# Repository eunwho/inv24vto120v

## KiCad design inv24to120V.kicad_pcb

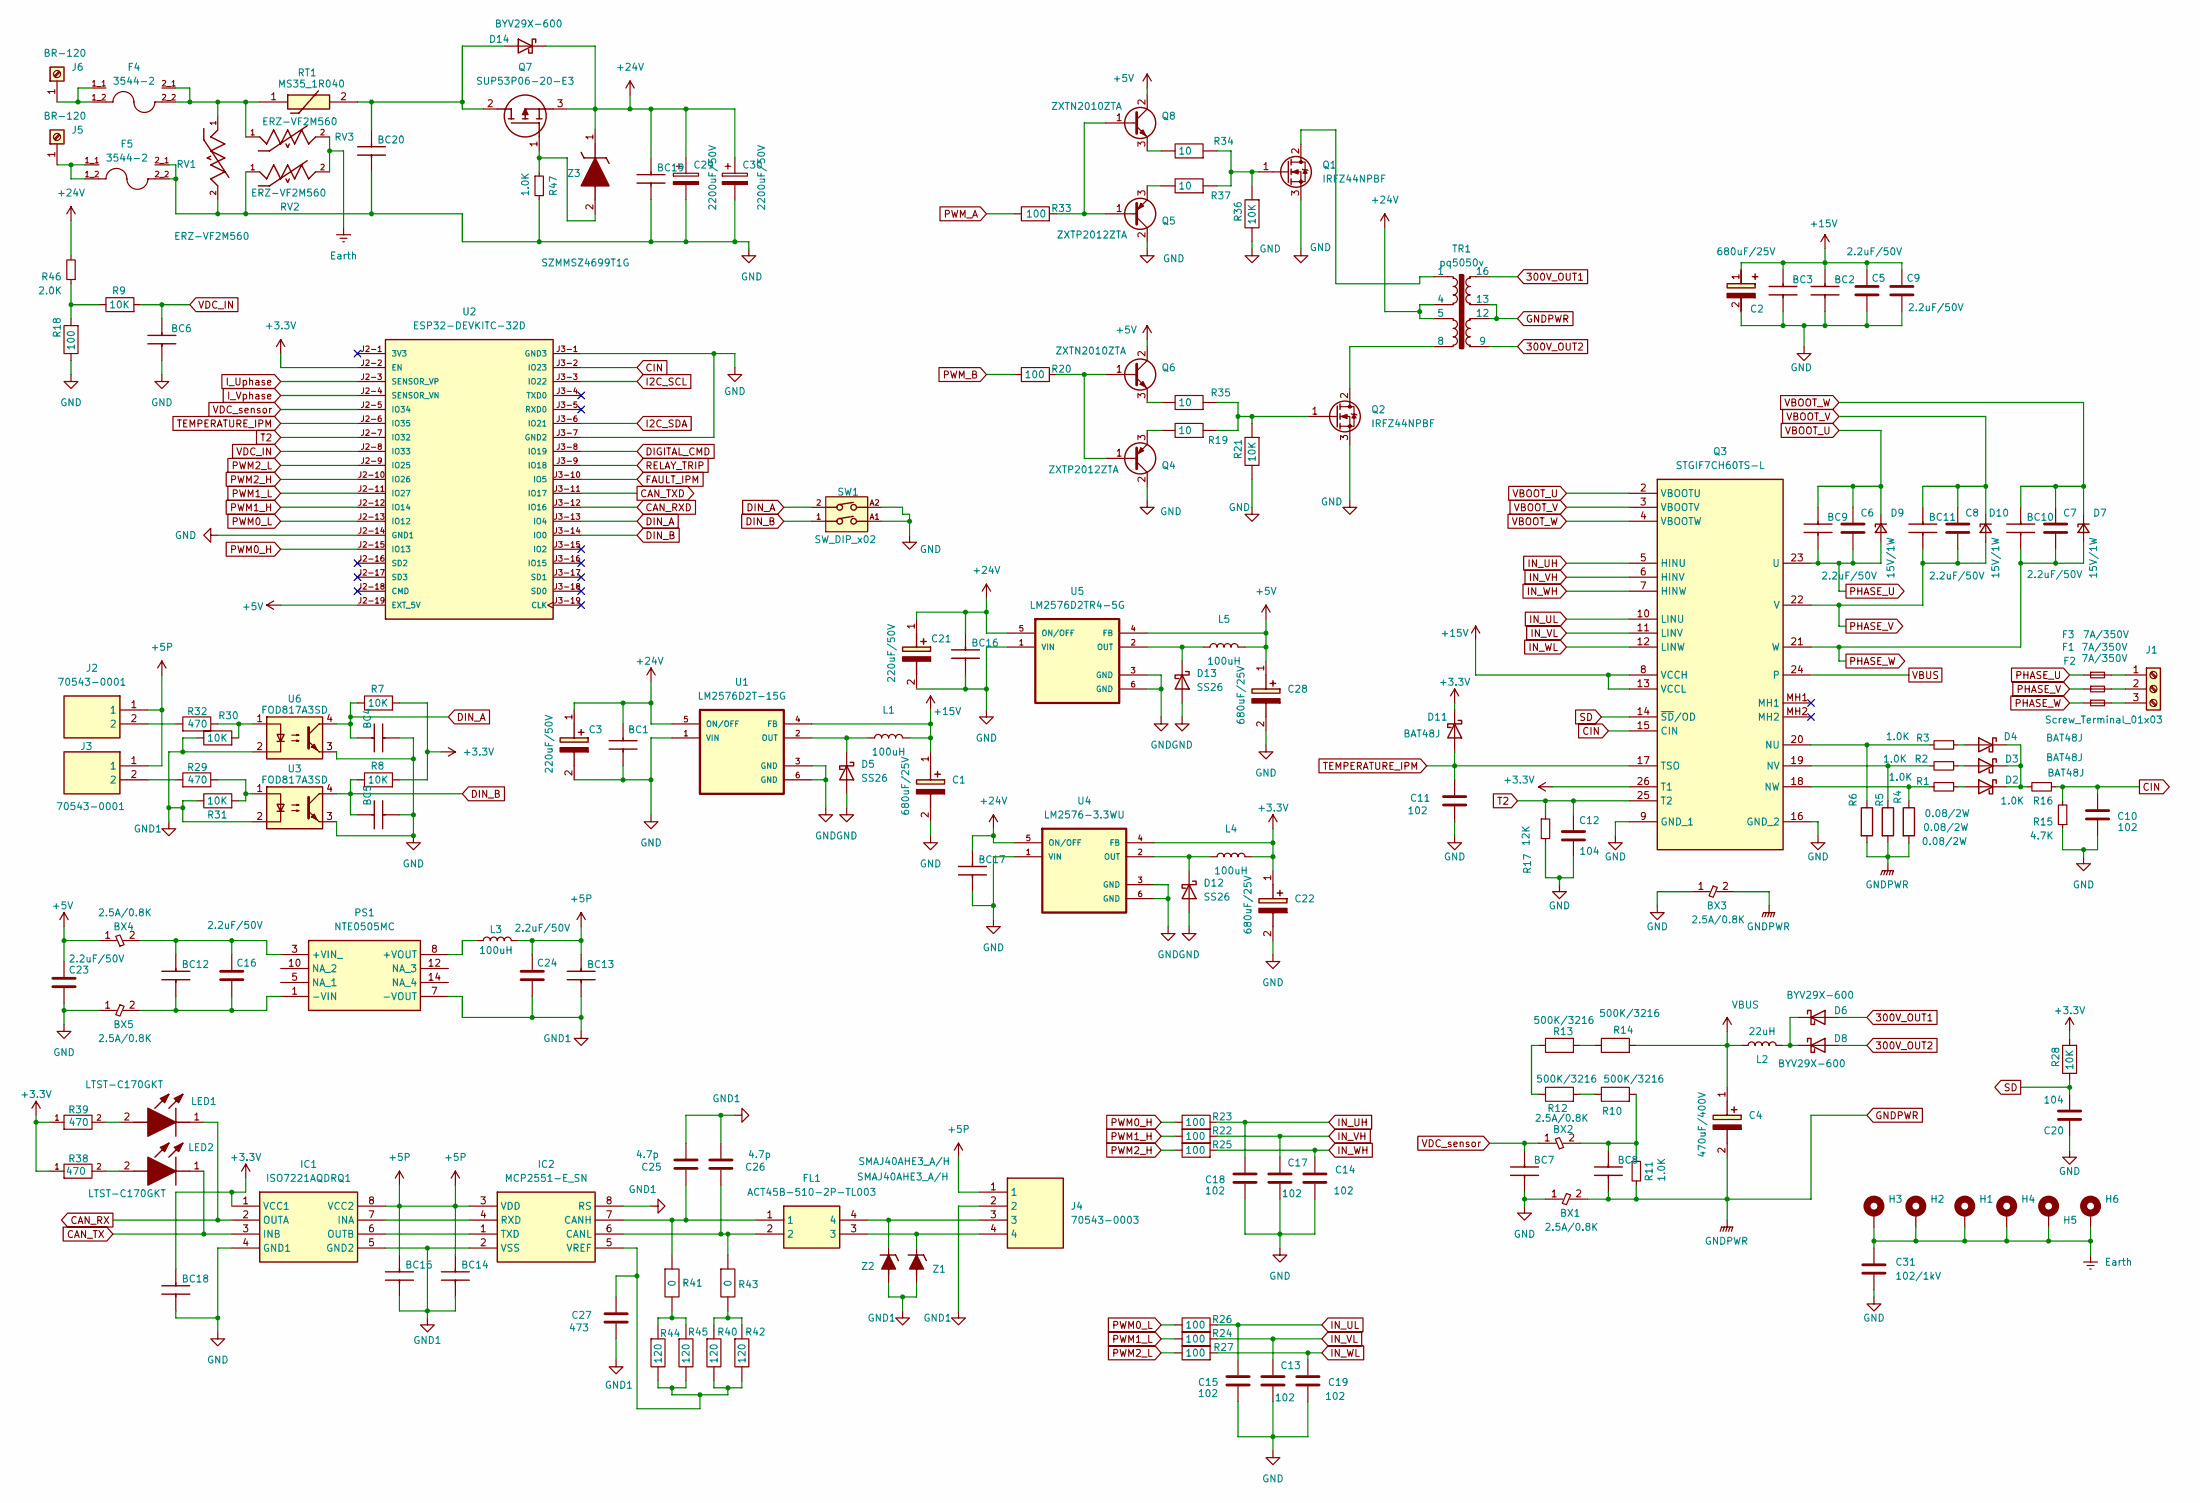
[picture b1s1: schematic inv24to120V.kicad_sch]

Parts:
BC1, BC2, BC3, BC4, BC5, BC6, BC7, BC8, BC9, BC10, BC11, BC12, BC13, BC14, BC15, BC16, BC17, BC18, BC19, BC20: 104/50V; CAPC2012X95N; Manufacturer_Part_Number CL21B104KBCNNNE; Mouser Part Number 187-CL21B104KBCNNNE
BX1, BX2, BX3, BX4, BX5: 2.5A/0.8K; BLM31KN102BH1L; Manufacturer_Part_Number BLM31KN801SH1L; Mouser Part Number 81-BLM31KN801SH1L
C1, C2, C22, C28: 680uF/25V; CP_Elec_16x17.5; Mouser Part Number 594-MAL226099603E3
C3, C21: 220uF/50V; CP_Elec_16x17.5; Mouser Part Number 594-MAL226099603E3
C4: 470uF/400V; CP_Radial_D35.0mm_P10.00mm_SnapIn; Mouser Part Number 647-LGX2G471MELC35
C5, C6, C7, C8, C9, C16, C23, C24: 2.2uF/50V; C_1206_3216Metric_Pad1.33x1.80mm_HandSolder; Manufacturer_Part_Number CL31A225KB9LNNC; Mouser Part Number 187-CL31A225KB9LNNC
C10, C11, C13, C14, C15, C17, C18, C19: 102; C_0805_2012Metric; Manufacturer_Part_Number CL21B102KBCNNNE; Mouser Part Number 187-CL21B104KBCNNNE
C12, C20: 104; C_0805_2012Metric; Manufacturer_Part_Number CL21B104KBCNNNE; Mouser Part Number 187-CL21B104KBCNNNE
C25, C26: 4.7p; C_0805_2012Metric; Manufacturer_Part_Number CL21B047PKBCNNNE; Mouser Part Number 187-CL21B473KBCNNNE
C27: 473; C_0805_2012Metric; Manufacturer_Part_Number CL21B473KBCNNNE; Mouser Part Number 187-CL21B473KBCNNNE
C29, C30: 2200uF/50V; CP_Radial_D18.0mm_P7.50mm; Manufacturer_Part_Number NXA 50V 2200uF
C31: 102/1kV; C_1812_4532Metric_Pad1.57x3.40mm_HandSolder; Manufacturer_Part_Number VJ1808Y103KXGAT; Mouser Part Number 77-VJ1808Y103KXGAT
D2, D3, D4, D11: BAT48J; D_SOD-323_HandSoldering; Mouser Part Number 511-BAT48JFILM
D5, D12, D13: SS26; DIOM5127X229N; Mouser Part Number 78-SS26SHE3_B/H
D6, D8: BYV29X-600; TO-220-2_Horizontal_TabUp; Mouser Part Number 771-BYV29X-600127
D7, D9, D10: 15V/1W; D_SMA_Handsoldering; Manufacturer_Part_Number SZ1SMA5929BT3G; Mouser Part Number 863-SZ1SMA5929BT3G
D14: BYV29X-600; TO507P1020X460X2000-2; Mouser Part Number 771-BYV29X-600127
F1, F2, F3: 7A/350V; Fuse_2512_6332Metric_Pad1.52x3.35mm_HandSolder; Mouser Part Number 530-0679H7000-05
F4, F5: 3544-2; FUSE_3544-2; Mouser Part Number 534-3544-2
FL1: ACT45B-510-2P-TL003; ACT45B1012PTL003; Mouser Part Number 810-ACT45B5102PTL003
H1, H2, H3, H4, H5, H6: MountingHole_Pad; MountingHole_4.3mm_M4_Pad_Via
IC1: ISO7221AQDRQ1; SOIC127P600X175-8N; Mouser Part Number 595-ISO7221AQDRQ1
IC2: MCP2551-E_SN; SOIC127P600X175-8N; Mouser Part Number 579-MCP2551-E/SN
J1: Screw_Terminal_01x03; TerminalBlock_Dinkle_DT-55-B01X-03_P10.00mm; Manufacturer_Part_Number BR-1000C(3핀); Mouser Part Number 디바이스마트 BR-1000C(3핀)
J2, J3: 70543-0001; SHDR2W64P0X254_1X2_737X660X1181P; Mouser Part Number 538-70543-0001
J4: 70543-0003; SHDR4W97P0X254_1X4_1271X660X1143P; Mouser Part Number 538-70543-0003
J5, J6: BR-120; Wuerth_REDCUBE-THR_WP-THRBU_74650073_THR; Manufacturer_Part_Number BR-120
L1, L3, L4, L5: 100uH; INDPM120120X600N; Manufacturer_Part_Number 7447706101; Mouser Part Number 710-7447706101
L2: 22uH; IND_HCTI-10-20.0; Manufacturer_Part_Number RING COIL 21파이(22uH)
LED1, LED2: LTST-C170GKT; LEDC2012X120N; Mouser Part Number 859-LTST-C170GKT
PS1: NTE0505MC; Mouser Part Number 580-NTE0505MC
Q1, Q2: IRFZ44NPBF; TO-220-3_Horizontal_TabUp; Manufacturer_Part_Number IRFZ44NPBF; Mouser Part Number 942-IRFZ44NPBF
Q3: STGIF7CH60TS-L; STGIB20M60TSL; Mouser Part Number 511-STGIF7CH60TS-L
Q4, Q5: ZXTP2012ZTA; SOT-89-3; Manufacturer_Part_Number ZXTP2012ZTA; Mouser Part Number 522-ZXTP2012ZTA
Q6, Q8: ZXTN2010ZTA; SOT-89-3; Manufacturer_Part_Number ZXTN2010ZTA; Mouser Part Number 522-ZXTN2010ZTA
Q7: SUP53P06-20-E3; TO-220-3_Horizontal_TabUp; Manufacturer_Part_Number SUP53P06-20-E3; Mouser Part Number 781-SUP53P06-20-E3
R1, R2, R3, R11, R16, R47: 1.0K; R_1206_3216Metric_Pad1.30x1.75mm_HandSolder; Mouser Part Number 71-RCC12061K00FKEA
R4, R5, R6: 0.08/2W; R_2816_7142Metric_Pad3.20x4.45mm_HandSolder; Mouser Part Number 71-WSL2816R0800FEH
R7, R8, R9, R21, R28, R30, R31, R36: 10K; R_0805_2012Metric_Pad1.20x1.40mm_HandSolder; Manufacturer_Part_Number RC2012J103CS; Mouser Part Number Nop
R10, R12, R13, R14: 500K/3216; R_1206_3216Metric_Pad1.30x1.75mm_HandSolder; Manufacturer_Part_Number CRMA1206AF500KFKEF; Mouser Part Number 71-CRMA1206AF500KFKF
R15: 4.7K; R_1206_3216Metric_Pad1.30x1.75mm_HandSolder; Mouser Part Number 71-RCC12064K70FKEA
R17: 12K; R_1206_3216Metric_Pad1.30x1.75mm_HandSolder; Mouser Part Number 71-RCC120612K0FKEA
R18, R20, R22, R23, R24, R25, R26, R27, R33: 100; R_0805_2012Metric_Pad1.20x1.40mm_HandSolder; Manufacturer_Part_Number RC2012J101CS; Mouser Part Number Nop
R19, R34, R35, R37: 10; R_0805_2012Metric_Pad1.20x1.40mm_HandSolder; Manufacturer_Part_Number RC2012J100CS; Mouser Part Number Nop
R29, R32, R38, R39: 470; R_0805_2012Metric_Pad1.20x1.40mm_HandSolder; Manufacturer_Part_Number RC2012J121CS; Mouser Part Number Nop
R40, R42, R44, R45: 120; R_0805_2012Metric_Pad1.20x1.40mm_HandSolder; Manufacturer_Part_Number RC2012J121CS; Mouser Part Number Nop
R41, R43: 0; R_0805_2012Metric_Pad1.20x1.40mm_HandSolder; Manufacturer_Part_Number RC2012J000CS; Mouser Part Number Nop
R46: 2.0K; R_1206_3216Metric_Pad1.30x1.75mm_HandSolder; Mouser Part Number 71-RCC12062K00FKEA
RT1: MS35_1R040; MS351R040; Manufacturer_Part_Number MS35 1R040; Mouser Part Number 995-MS35-1R040
RV1, RV2, RV3: ERZ-VF2M560; VAR_ERZ-VF2M560; Manufacturer_Part_Number ERZ-VF2M560; Mouser Part Number 667-ERZ-VF2M560
SW1: SW_DIP_x02; 418117270902; Manufacturer_Part_Number 418117270902; Mouser Part Number 710-418117270902
TR1: pq5050v; pq5050h; Manufacturer_Part_Number PQ5050-24-300-6PV; Mouser Part Number Nop
U1: LM2576D2T-15G; KTT0005B; Manufacturer_Part_Number LM2576D2T-15G; Mouser Part Number 863-LM2576D2T-15G
U2: ESP32-DEVKITC-32D; MODULE_ESP32-DEVKITC-32D; Manufacturer_Part_Number DLT-dspModule_241; Mouser Part Number Nop
U3, U6: FOD817A3SD; PDIP4GW_709AH_ONS-M; Manufacturer_Part_Number 호: FOD817A3SD; Mouser Part Number 512-FOD817A3SD
U4: LM2576-3.3WU; KTT0005B; Manufacturer_Part_Number LM2576-3.3WU; Mouser Part Number 998-LM2576-3.3WU
U5: LM2576D2TR4-5G; KTT0005B; Manufacturer_Part_Number LM2576D2TR4-5G; Mouser Part Number 863-LM2576D2TR4-5G
Z1, Z2: SMAJ40AHE3_A/H; DIOM5027X244N; Mouser Part Number 78-SMAJ40AHE3_A/H
Z3: SZMMSZ4699T1G; SOD3716X135N; Manufacturer_Part_Number SZMMSZ4699T1G; Mouser Part Number 863-SZMMSZ4699T1G

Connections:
300V_OUT1: D6.2 (A), TR1.16
300V_OUT2: D8.2 (A), TR1.9
+3.3V: BC18.1, C22.1 (+), D11.1 (K), IC1.1 (VCC1), L4.2, Q3.26 (T1), R7.1, R8.1, R28.1, R38.1, R39.1, U2.J2-2 (EN), U4.4 (FB)
+5P: BC13.1, BC14.1, BC15.1, C24.1, IC1.8 (VCC2), IC2.3 (VDD), J2.1, J3.1, J4.1, L3.2
+5V: BX4.1, C23.1, C28.1 (+), L5.2, Q6.2 (C), Q8.2 (C), U2.J2-19 (EXT_5V), U5.4 (FB)
+15V: BC2.1, BC3.1, C1.1 (+), C2.1 (+), C5.1, C9.1, L1.2, Q3.8 (VCCH), Q3.13 (VCCL), U1.4 (FB)
+24V: BC1.1, BC16.1, BC17.1, BC19.1, C3.1 (+), C21.1 (+), C29.1, C30.1, D14.1 (K), Q7.3 (S), R46.2, TR1.4, TR1.5, U1.5 (ON/OFF), U4.5 (ON/OFF), U5.5 (ON/OFF), Z3.1 (K)
CAN_RX: IC1.2 (OUTA), LED1.1 (K)
CAN_RXD: U2.J3-12 (IO16)
CAN_TX: IC1.3 (INB), LED2.1 (K)
CAN_TXD: U2.J3-11 (IO17)
CIN: C10.1, Q3.15 (CIN), R15.2, R16.1, U2.J3-2 (IO23)
DIGITAL_CMD: U2.J3-8 (IO19)
DIN_A: BC4.1, R7.2, SW1.2, U2.J3-13 (IO4), U6.4
DIN_B: BC5.1, R8.2, SW1.1, U2.J3-14 (IO0), U3.4
Earth: C31.1, H1.1, H2.1, H3.1, H4.1, H5.1, H6.1, RV2.2, RV3.2
FAULT_IPM: U2.J3-10 (IO5)
GND: BC1.2, BC2.2, BC3.2, BC4.2, BC5.2, BC6.2, BC7.2, BC16.2, BC17.2, BC18.2, BC19.2, BC20.2, BX1.1, BX3.1, BX5.1, C1.2 (-), C2.2 (-), C3.2 (-), C5.2, C9.2, C10.2, C11.2, C12.2, C13.2, C14.2, C15.2, C17.2, C18.2, C19.2, C20.1, C21.2 (-), C22.2 (-), C23.2, C28.2 (-), C29.2, C30.2, C31.2, D5.2 (A), D12.2 (A), D13.2 (A), F5.2_1, F5.2_2, IC1.4 (GND1), Q1.3 (S), Q2.3 (S), Q3.9 (GND_1), Q3.16 (GND_2), Q4.2 (C), Q5.2 (C), R15.1, R17.2, R18.2, R21.2, R36.2, R47.2, RV1.2, RV2.1, SW1.A1, SW1.A2, U1.1 (VIN), U1.3 (GND), U1.6 (GND), U2.J2-14 (GND1), U2.J3-1 (GND3), U2.J3-7 (GND2), U3.3, U4.1 (VIN), U4.3 (GND), U4.6 (GND), U5.1 (VIN), U5.3 (GND), U5.6 (GND), U6.3
GND1: BC13.2, BC14.2, BC15.2, C24.2, C25.2, C26.2, C27.2, IC1.5 (GND2), IC2.2 (VSS), IC2.8 (RS), J4.2, PS1.7 (-VOUT), R30.2, R31.2, U3.2, U6.2, Z1.2 (A), Z2.2 (A)
GNDPWR: BC8.2, BX1.2, BX3.2, C4.2 (-), R4.2, R5.2, R6.2, R11.2, TR1.12, TR1.13
I2C_SCL: U2.J3-3 (IO22)
I2C_SDA: U2.J3-6 (IO21)
IN_UH: C18.1, Q3.5 (HINU), R23.1
IN_UL: C15.1, Q3.10 (LINU), R26.1
IN_VH: C17.1, Q3.6 (HINV), R22.1
IN_VL: C13.1, Q3.11 (LINV), R24.1
IN_WH: C14.1, Q3.7 (HINW), R25.1
IN_WL: C19.1, Q3.12 (LINW), R27.1
I_Uphase: U2.J2-3 (SENSOR_VP)
I_Vphase: U2.J2-4 (SENSOR_VN)
unnamed: BC8.1, BX2.2, R10.1, R11.1
unnamed: BC20.1, D14.2 (A), Q7.2 (D), RT1.2
unnamed: D12.1 (K), L4.1, U4.2 (OUT)
unnamed: D13.1 (K), L5.1, U5.2 (OUT)
unnamed: D6.1 (K), D8.1 (K), L2.2
unnamed: D5.1 (K), L1.1, U1.2 (OUT)
unnamed: D2.2 (A), R1.1
unnamed: D2.1 (K), D3.1 (K), D4.1 (K), R16.2
unnamed: D3.2 (A), R2.1
unnamed: D4.2 (A), R3.1
unnamed: F4.2_1, F4.2_2, RT1.1, RV1.1, RV3.1
unnamed: C25.1, FL1.1, IC2.7 (CANH), R41.1
unnamed: C26.1, FL1.2, IC2.6 (CANL), R43.1
unnamed: IC1.7 (INA), IC2.4 (RXD)
unnamed: IC1.6 (OUTB), IC2.1 (TXD)
unnamed: C27.1, IC2.5 (VREF), R40.2, R42.2, R44.2, R45.2
unnamed: J2.2, R32.1
unnamed: J3.2, R29.1
unnamed: F3.2, J1.1
unnamed: F1.2, J1.2
unnamed: F2.2, J1.3
unnamed: F5.1_1, F5.1_2, J5.1
unnamed: F4.1_1, F4.1_2, J6.1
unnamed: LED1.2 (A), R39.2
unnamed: LED2.2 (A), R38.2
unnamed: BC12.1, BX4.2, C16.1, PS1.3 (+VIN_)
unnamed: L3.1, PS1.8 (+VOUT)
unnamed: BC12.2, BX5.2, C16.2, PS1.1 (-VIN)
unnamed: Q1.2 (D), TR1.1
unnamed: Q1.1 (G), R34.1, R36.1, R37.1
unnamed: Q2.2 (D), TR1.8
unnamed: Q2.1 (G), R19.1, R21.1, R35.1
unnamed: Q5.1 (B), Q8.1 (B), R33.1
unnamed: Q8.3 (E), R34.2
unnamed: Q4.1 (B), Q6.1 (B), R20.1
unnamed: Q6.3 (E), R35.2
unnamed: Q5.3 (E), R37.2
unnamed: Q4.3 (E), R19.2
unnamed: Q7.1 (G), R47.1, Z3.2 (A)
unnamed: Q3.20 (NU), R3.2, R6.1
unnamed: Q3.19 (NV), R2.2, R5.1
unnamed: Q3.18 (NW), R1.2, R4.1
unnamed: R41.2, R44.1, R45.1
unnamed: R40.1, R42.1, R43.2
unnamed: R13.1, R14.2
unnamed: R12.2, R13.2
unnamed: R10.2, R12.1
unnamed: R9.2, R18.1, R46.1
unnamed: R30.1, R32.2, U6.1
unnamed: R29.2, R31.1, U3.1
unnamed: FL1.3, J4.4, Z1.1 (K)
unnamed: FL1.4, J4.3, Z2.1 (K)
PHASE_U: BC9.2, C6.2, D9.2 (A), F3.1, Q3.23 (U); also elsewhere on the board
PHASE_V: BC11.2, C8.2, D10.2 (A), F1.1, Q3.22 (V); also elsewhere on the board
PHASE_W: BC10.2, C7.2, D7.2 (A), F2.1, Q3.21 (W)
PWM0_H: R23.2, U2.J2-15 (IO13)
PWM0_L: R26.2, U2.J2-13 (IO12)
PWM1_H: R22.2, U2.J2-12 (IO14)
PWM1_L: R24.2, U2.J2-11 (IO27)
PWM2_H: R25.2, U2.J2-10 (IO26)
PWM2_L: R27.2, U2.J2-9 (IO25)
PWM_A: R33.2
PWM_B: R20.2
RELAY_TRIP: U2.J3-9 (IO18)
SD: C20.2, Q3.14 (~SD/OD), R28.2
T2: C12.1, Q3.25 (T2), R17.1, U2.J2-7 (IO32)
TEMPERATURE_IPM: C11.1, D11.2 (A), Q3.17 (TSO), U2.J2-6 (IO35)
VBOOT_U: BC9.1, C6.1, D9.1 (K), Q3.2 (VBOOTU)
VBOOT_V: BC11.1, C8.1, D10.1 (K), Q3.3 (VBOOTV)
VBOOT_W: BC10.1, C7.1, D7.1 (K), Q3.4 (VBOOTW)
VBUS: C4.1 (+), L2.1, Q3.24, R14.1
VDC_IN: BC6.1, R9.1, U2.J2-8 (IO33)
VDC_sensor: BC7.1, BX2.1, U2.J2-5 (IO34)

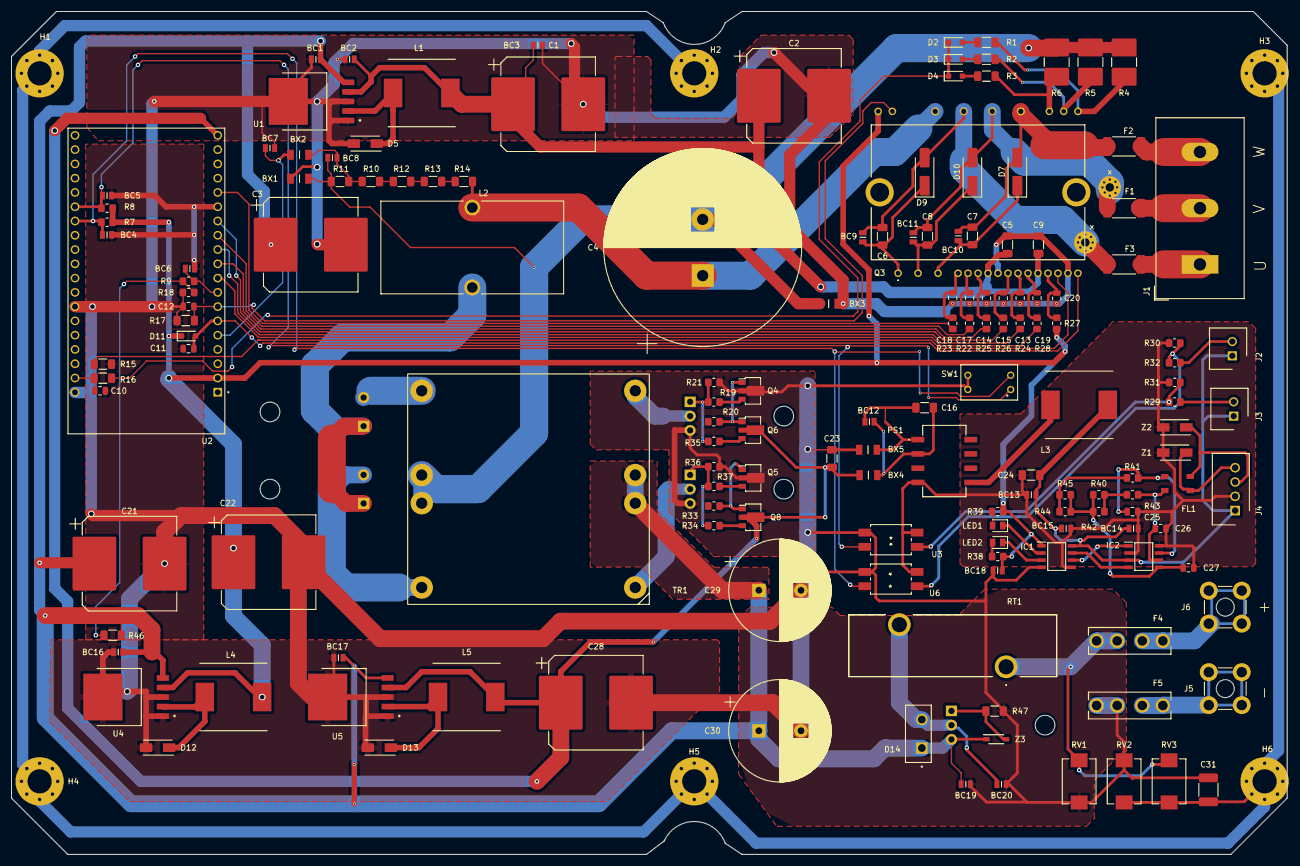
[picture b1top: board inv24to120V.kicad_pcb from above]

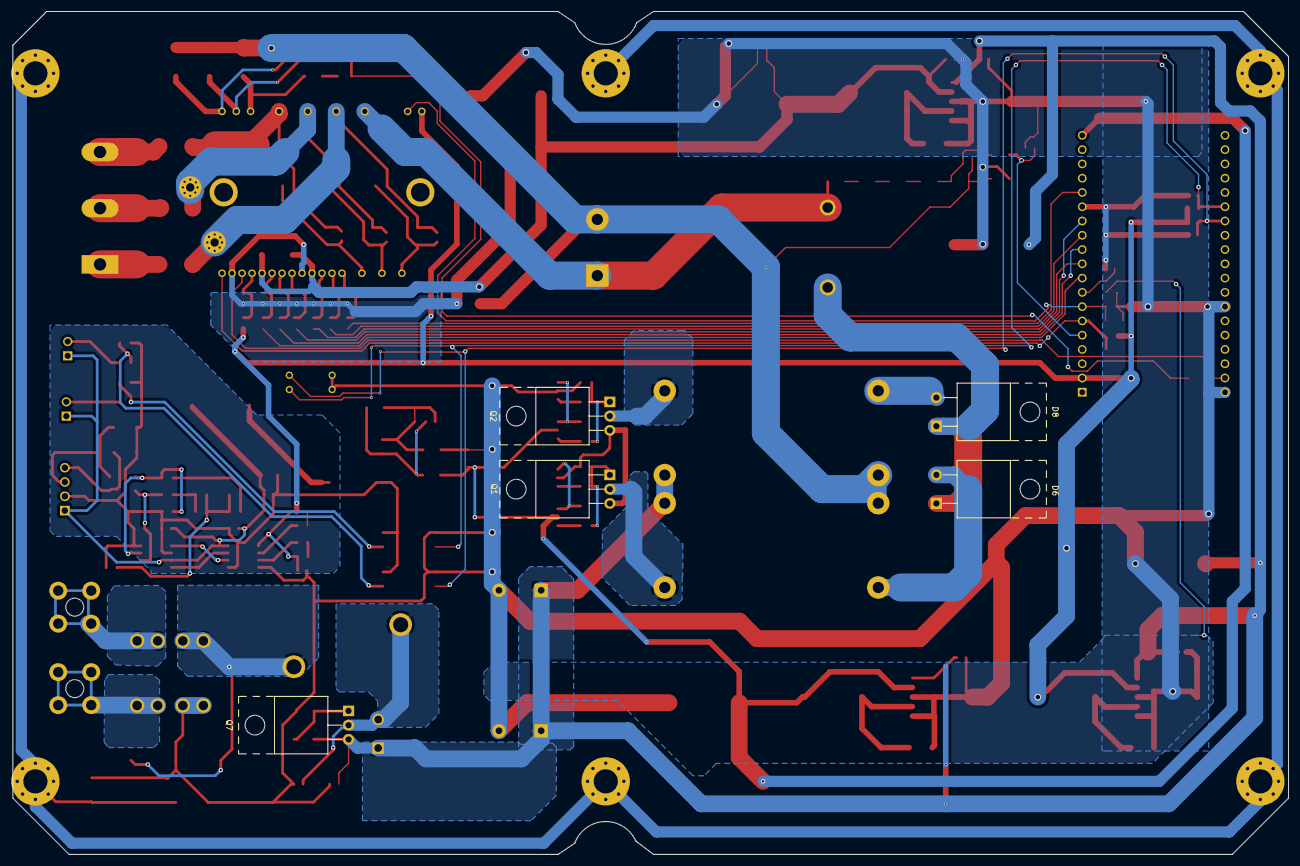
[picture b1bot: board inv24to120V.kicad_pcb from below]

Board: 2 copper layers, 227.0 x 150.0 mm, 169 parts (5 on the bottom side), 92 nets.

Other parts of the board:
x: via_power_out
x#2: via_power_out

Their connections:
PHASE_U: x#2.1; also elsewhere on the board
PHASE_V: x.1; also elsewhere on the board

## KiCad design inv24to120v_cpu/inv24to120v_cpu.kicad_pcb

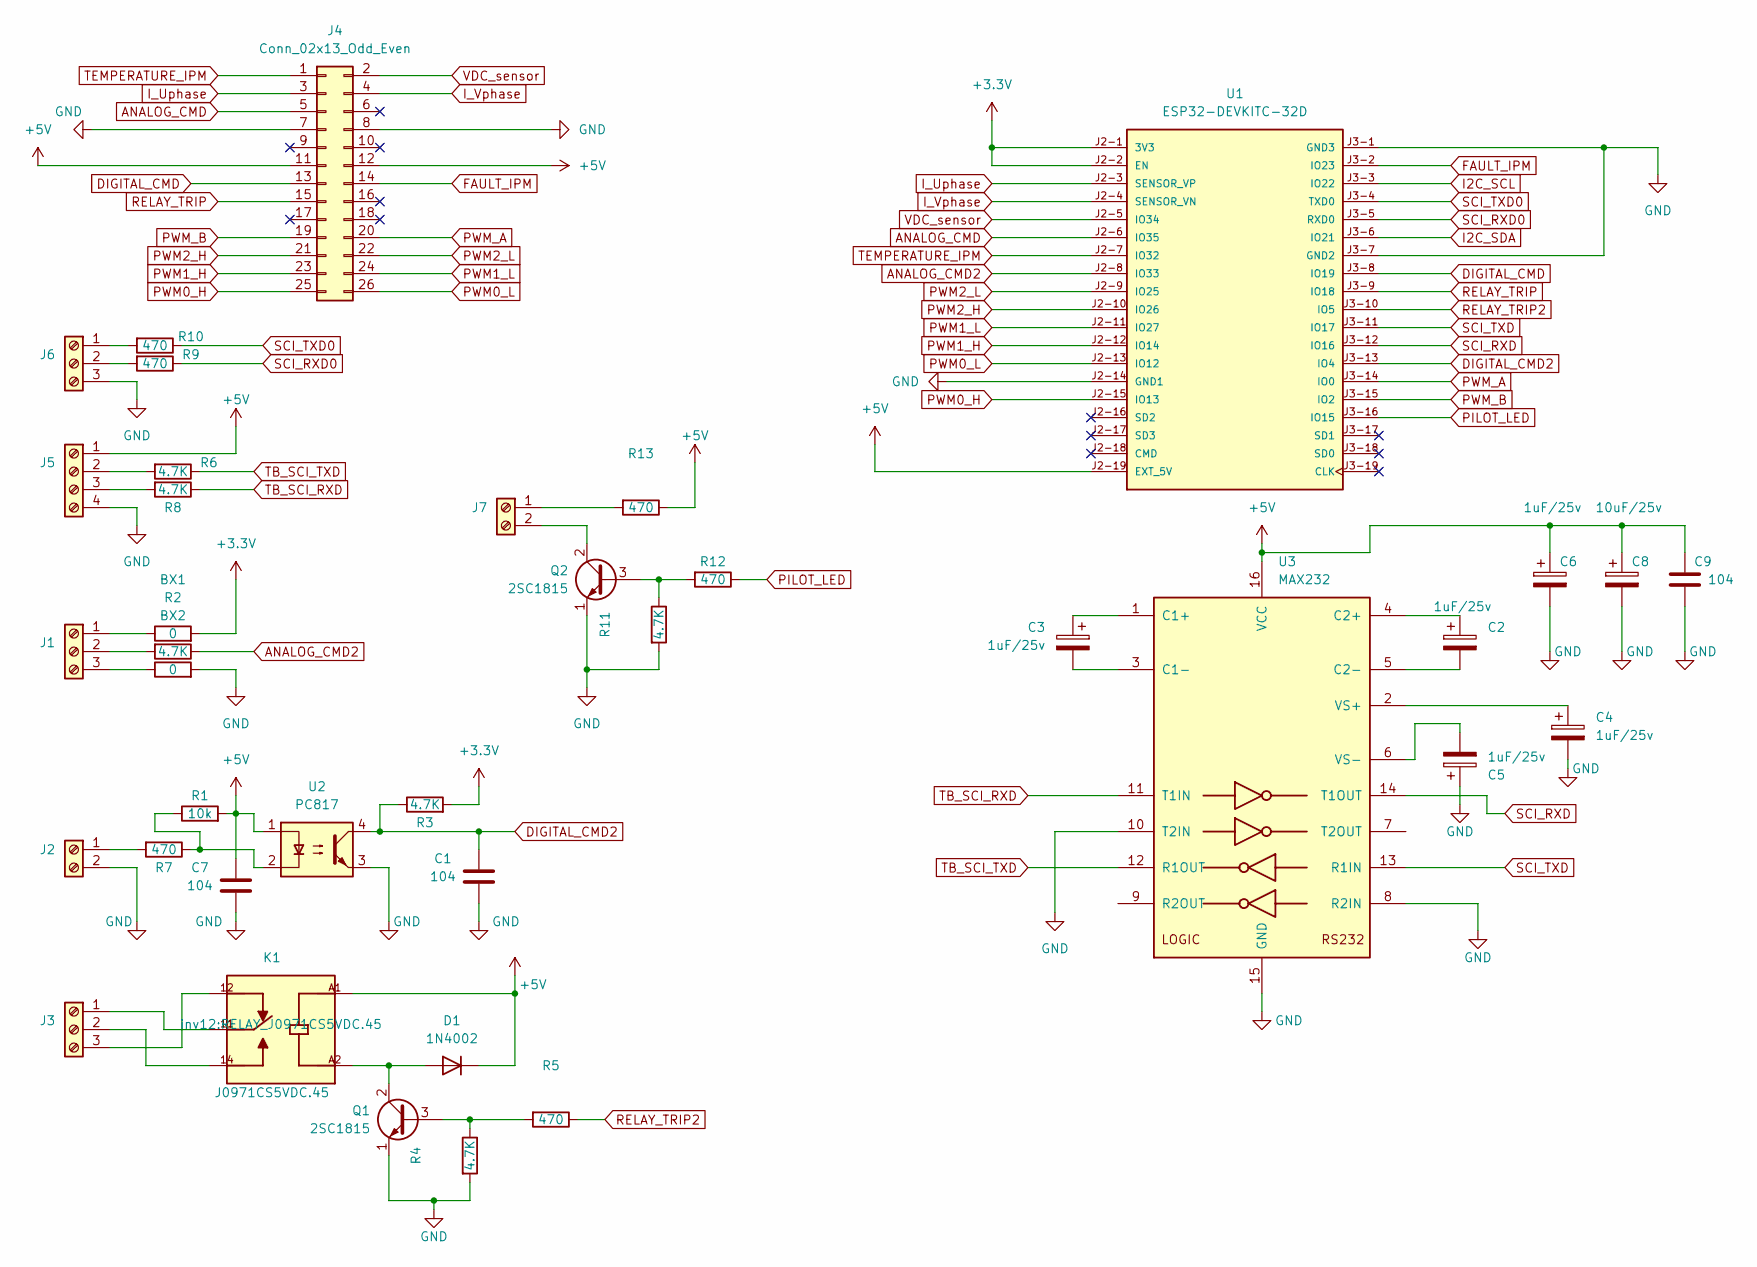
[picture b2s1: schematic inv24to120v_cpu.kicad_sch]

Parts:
BX1, BX2: 0; R_Axial_DIN0207_L6.3mm_D2.5mm_P10.16mm_Horizontal
C1, C7, C9: 104; C_Axial_L3.8mm_D2.6mm_P7.50mm_Horizontal
C2, C3, C4, C5, C6: 1uF/25v; CP_Radial_D5.0mm_P2.50mm
C8: 10uF/25v; CP_Radial_D5.0mm_P2.50mm
D1: 1N4002; D_DO-41_SOD81_P10.16mm_Horizontal
J1, J5, J6: Screw_Terminal_01x03; TerminalBlock_Phoenix_MKDS-1,5-3-5.08_1x03_P5.08mm_Horizont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
J2, J7: Screw_Terminal_01x02; TerminalBlock_Phoenix_MKDS-1,5-2-5.08_1x02_P5.08mm_Horizont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
J3: Screw_Terminal_01x03; TerminalBlock_Phoenix_MKDS-1,5-3_1x03_P5.00mm_Horizontal
J4: Conn_02x13_Odd_Even; Hirose_DF11-26DP-2DSA_2x13_P2.00mm_Vertical
K1: J0971CS5VDC.45; RELAY_J0971CS5VDC.45; PARTREV --
Q1, Q2: 2SC1815; TO-92_Inline
R1: 10k; R_Axial_DIN0207_L6.3mm_D2.5mm_P10.16mm_Horizontal
R2, R3, R4, R6, R8, R11: 4.7K; R_Axial_DIN0207_L6.3mm_D2.5mm_P10.16mm_Horizontal
R5, R7, R9, R10, R12, R13: 470; R_Axial_DIN0207_L6.3mm_D2.5mm_P10.16mm_Horizontal
U1: ESP32-DEVKITC-32D; MODULE_ESP32-DEVKITC-32D; PARTREV V4
U2: PC817; DIP-4_W7.62mm
U3: MAX232; DIP-16_W7.62mm_Socket

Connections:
+3.3V: BX1.2, R3.2, U1.J2-1 (3V3), U1.J2-2 (EN)
+5V: C6.1, C7.2, C8.1, C9.2, D1.1 (K), J4.11, J4.12, J5.1, K1.A1, R1.2, R13.1, U1.J2-19 (EXT_5V), U2.1, U3.16 (VCC)
ANALOG_CMD: J4.5, U1.J2-6 (IO35)
ANALOG_CMD2: R2.1, U1.J2-8 (IO33)
DIGITAL_CMD: J4.13, U1.J3-8 (IO19)
DIGITAL_CMD2: C1.2, R3.1, U1.J3-13 (IO4), U2.4
FAULT_IPM: J4.14, U1.J3-2 (IO23)
GND: BX2.2, C1.1, C4.2, C5.1, C6.2, C7.1, C8.2, C9.1, J2.2, J4.7, J4.8, J5.4, J6.3, Q1.1 (E), Q2.1 (E), R4.2, R11.2, U1.J2-14 (GND1), U1.J3-1 (GND3), U1.J3-7 (GND2), U2.3, U3.8 (R2IN), U3.10 (T2IN), U3.15 (GND)
I2C_SCL: U1.J3-3 (IO22)
I2C_SDA: U1.J3-6 (IO21)
I_Uphase: J4.3, U1.J2-3 (SENSOR_VP)
I_Vphase: J4.4, U1.J2-4 (SENSOR_VN)
unnamed: D1.2 (A), K1.A2, Q1.2 (C)
unnamed: BX1.1, J1.1
unnamed: J1.2, R2.2
unnamed: BX2.1, J1.3
unnamed: J2.1, R7.2
unnamed: J3.1, K1.11
unnamed: J3.2, K1.14
unnamed: J3.3, K1.12
unnamed: J5.2, R6.2
unnamed: J5.3, R8.2
unnamed: J6.1, R10.2
unnamed: J6.2, R9.2
unnamed: J7.1, R13.2
unnamed: J7.2, Q2.2 (C)
unnamed: Q1.3 (B), R4.1, R5.2
unnamed: Q2.3 (B), R11.1, R12.2
unnamed: R1.1, R7.1, U2.2
unnamed: C3.1, U3.1 (C1+)
unnamed: C3.2, U3.3 (C1-)
unnamed: C2.1, U3.4 (C2+)
unnamed: C2.2, U3.5 (C2-)
unnamed: C4.1, U3.2 (VS+)
unnamed: C5.2, U3.6 (VS-)
PILOT_LED: R12.1, U1.J3-16 (IO15)
PWM0_H: J4.25, U1.J2-15 (IO13)
PWM0_L: J4.26, U1.J2-13 (IO12)
PWM1_H: J4.23, U1.J2-12 (IO14)
PWM1_L: J4.24, U1.J2-11 (IO27)
PWM2_H: J4.21, U1.J2-10 (IO26)
PWM2_L: J4.22, U1.J2-9 (IO25)
PWM_A: J4.20, U1.J3-14 (IO0)
PWM_B: J4.19, U1.J3-15 (IO2)
RELAY_TRIP: J4.15, U1.J3-9 (IO18)
RELAY_TRIP2: R5.1, U1.J3-10 (IO5)
SCI_RXD: U1.J3-12 (IO16), U3.14 (T1OUT)
SCI_RXD0: R9.1, U1.J3-5 (RXD0)
SCI_TXD: U1.J3-11 (IO17), U3.13 (R1IN)
SCI_TXD0: R10.1, U1.J3-4 (TXD0)
TB_SCI_RXD: R8.1, U3.11 (T1IN)
TB_SCI_TXD: R6.1, U3.12 (R1OUT)
TEMPERATURE_IPM: J4.1, U1.J2-7 (IO32)
VDC_sensor: J4.2, U1.J2-5 (IO34)

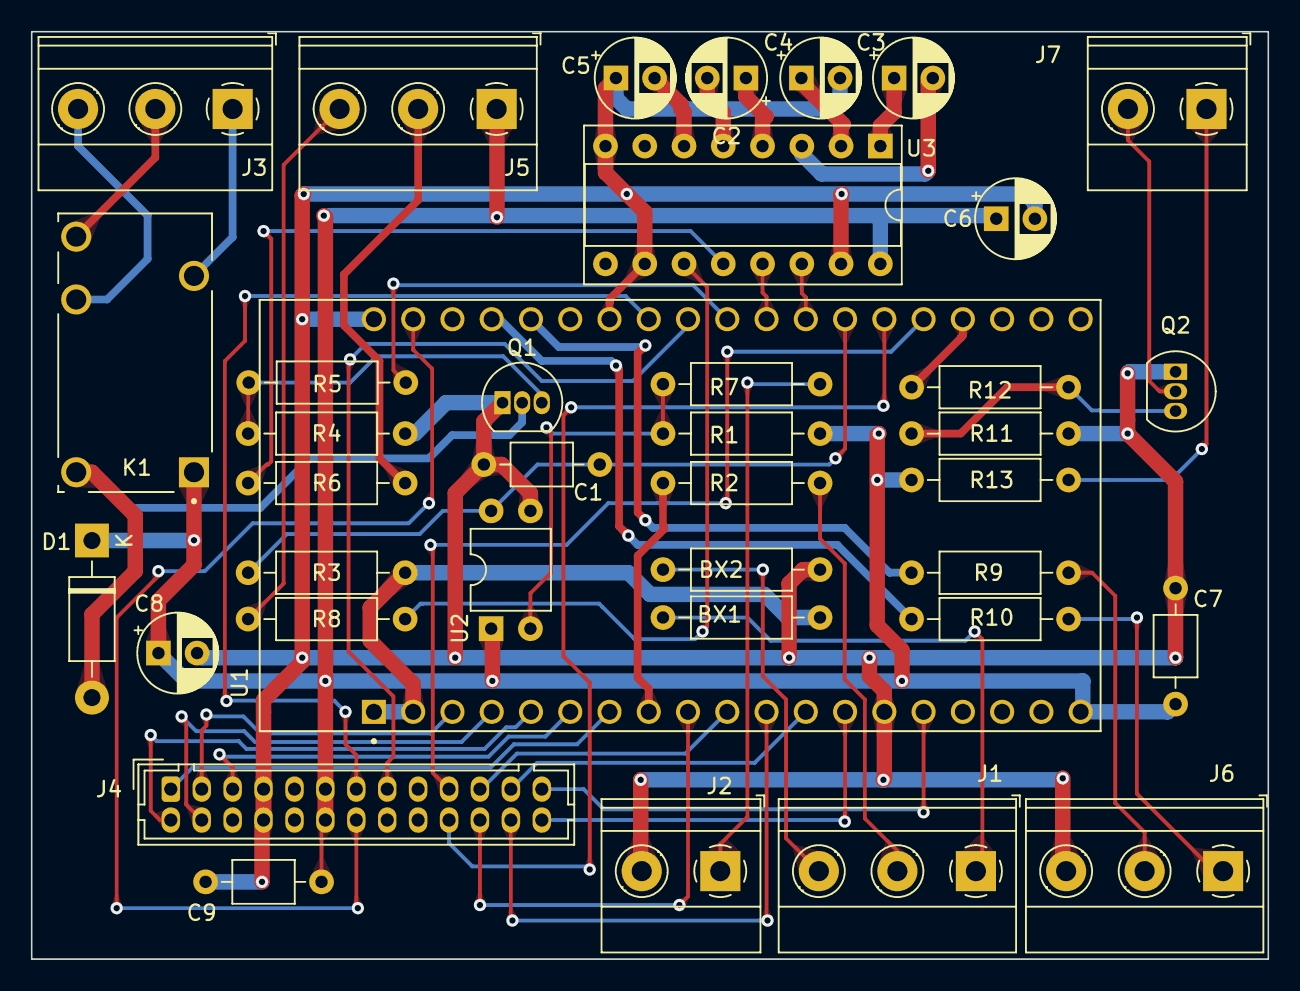
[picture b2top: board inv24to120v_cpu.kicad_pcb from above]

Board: 2 copper layers, 80.0 x 60.0 mm, 38 parts (0 on the bottom side), 52 nets.
